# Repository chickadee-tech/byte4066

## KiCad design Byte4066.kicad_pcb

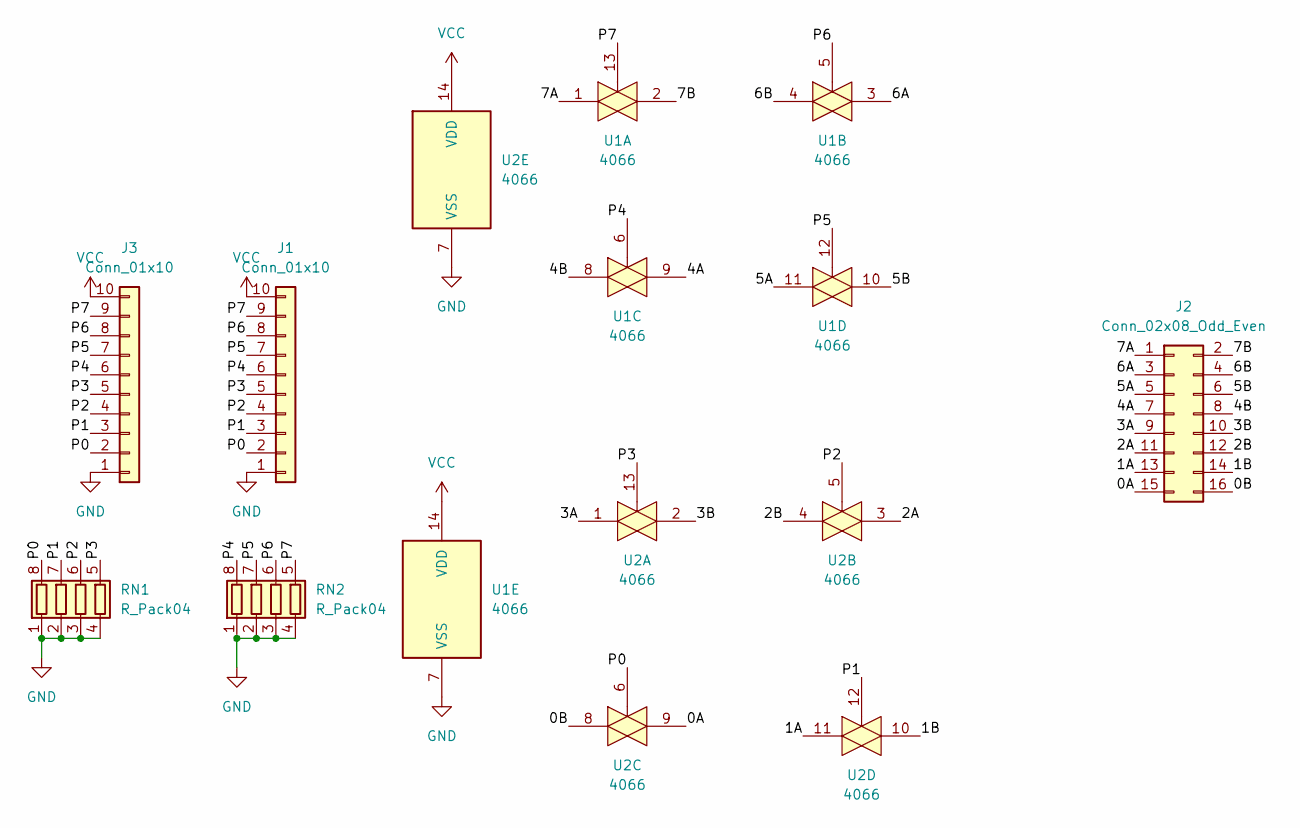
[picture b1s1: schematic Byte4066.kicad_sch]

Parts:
J1: Conn_01x10; PinSocket_1x10_P2.54mm_Vertical
J2: Conn_02x08_Odd_Even; PinHeader_2x08_P2.54mm_Horizontal
J3: Conn_01x10; 1x10 pads
RN1, RN2: R_Pack04; R_Array_Convex_4x0603
U1, U2: 4066; SOIC-14_3.9x8.7mm_P1.27mm

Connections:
/0A: J2.15, U2.9
/0B: J2.16, U2.8
/1A: J2.13, U2.11
/1B: J2.14, U2.10
/2A: J2.11, U2.3
/2B: J2.12, U2.4
/3A: J2.9, U2.1
/3B: J2.10, U2.2
/4A: J2.7, U1.9
/4B: J2.8, U1.8
/5A: J2.5, U1.11
/5B: J2.6, U1.10
/6A: J2.3, U1.3
/6B: J2.4, U1.4
/7A: J2.1, U1.1
/7B: J2.2, U1.2
/P0: J1.2, J3.2, RN1.8 (R1.2), U2.6
/P1: J1.3, J3.3, RN1.7 (R2.2), U2.12
/P2: J1.4, J3.4, RN1.6 (R3.2), U2.5
/P3: J1.5, J3.5, RN1.5 (R4.2), U2.13
/P4: J1.6, J3.6, RN2.8 (R1.2), U1.6
/P5: J1.7, J3.7, RN2.7 (R2.2), U1.12
/P6: J1.8, J3.8, RN2.6 (R3.2), U1.5
/P7: J1.9, J3.9, RN2.5 (R4.2), U1.13
GND: J1.1, J3.1, RN1.1 (R1.1), RN1.2 (R2.1), RN1.3 (R3.1), RN1.4 (R4.1), RN2.1 (R1.1), RN2.2 (R2.1), RN2.3 (R3.1), RN2.4 (R4.1), U1.7 (VSS), U2.7 (VSS)
VCC: J1.10, J3.10, U1.14 (VDD), U2.14 (VDD)

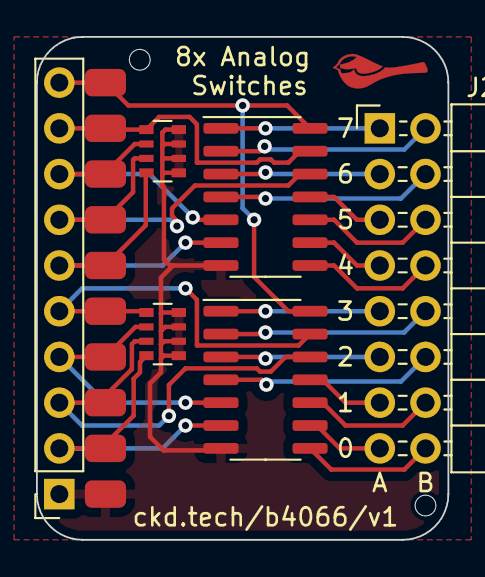
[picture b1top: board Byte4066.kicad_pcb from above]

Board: 2 copper layers, 22.9 x 27.9 mm, 7 parts (0 on the bottom side), 26 nets.

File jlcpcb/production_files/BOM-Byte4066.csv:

Comment,Designator,Footprint,LCSC
R_Pack04,"RN1,RN2",R_Array_Convex_4x0603,C29718
4066,"U1,U2",SOIC-14_3.9x8.7mm_P1.27mm,C54755

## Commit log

2022-12-02 not done yet
